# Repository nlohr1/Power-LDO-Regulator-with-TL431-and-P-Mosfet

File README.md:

# Power-LDO-Regulator with TL431 and P-Mosfet
Power-LDO to regulate voltages above +5V protecting USB-connectors from incoming overvoltages.

This Layout adds a simple way to eliminate dangerous incoming Over-Voltages on USB (above 5,25V) coming f.ex. from
odd Power-Supplies which don't acomplish the USB-specifications (but often are usable and cheap enough to be used as 5V-Supply).

Usually generic LDO-chips can output between 100 mAmp upto 1 Ampére. But what if you have a Power-Supply which can supply 4 or
more Amps but the voltage is too high for savely connect to the USB-Power-Input? (f.ex. on the new Raspberry Pi 4).
Most of commercial (Power-)LDO's need more than 3 Volts to be able to regulate the Output reliably. So the old LM7805 or even
the commonly used LM317(adj). And other mainly used chips as the AMS1117 normally only can provide upto 800mA. In most cases
this is sufficient power. But if you have a Power-Supply with an Output of (f.ex.) 5,5V and need to have an USB-Input with
a greater Power than 3 Amps, then you can go with this small layout, the board needing only few space (20 x 9 mm) and can
provide more than 4A – with a Heat-Sink and a more powerful Power-Mosfet even more than 10A...

Provided files here with 2 alternative solutions:
- first solution with a TL431-Shunt-Regulator + OPAmp and a *Power-P-Mosfet*,
- second solution with same TL431 + OPAmp but with a *Power-N-Mosfet*, due to this Mosfets generally have fewer resistance
  (=more "power"), are cheaper and there are more available types (of N-Mosfets) on the market (availability).

A caveat from this second solution is that it has only a common +5V line between Input and Output but no common Ground with the Main-Supply.
But on the other side this is mostly no problem for the End-Load, because the providing 5V-Main-Supplies normally are isolated-topologies,
so "GND" of the Destination-Load may be seen here simply as 5V-difference from our common +5V line.

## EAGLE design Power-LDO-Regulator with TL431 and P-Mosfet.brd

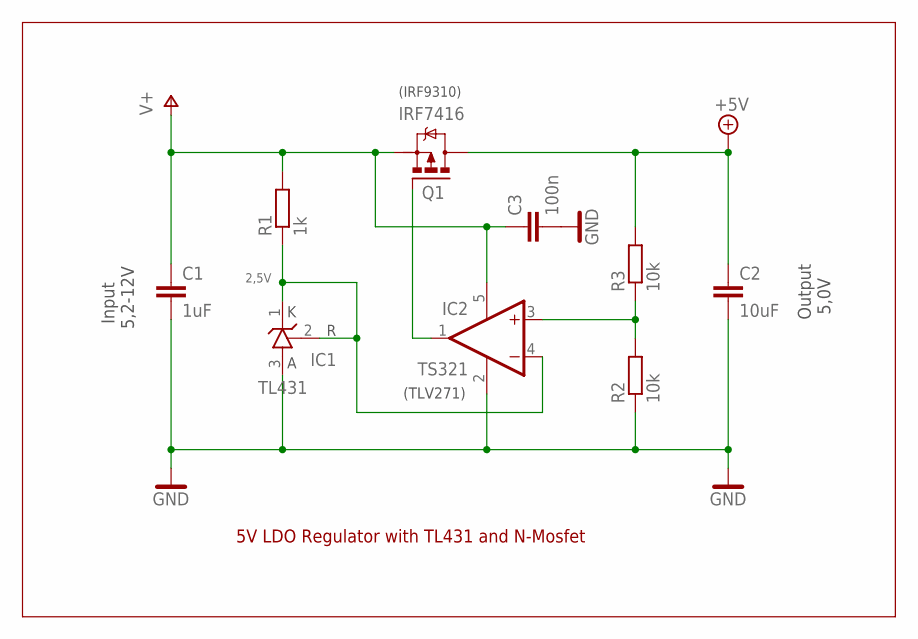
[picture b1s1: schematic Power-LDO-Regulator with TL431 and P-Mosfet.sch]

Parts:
C1: 1uF; C0805
C2: 10uF; C0805
C3: 100n; C0603
IC1: TL431; SOT23
IC2: TS321; SOT23-5
Q1: IRF7416; SO-08
R1: 1k; R0603
R2, R3: 10k; R0603

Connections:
+5V: C2.1, Q1.5 (D), Q1.6 (D), Q1.7 (D), Q1.8 (D), R3.2
GND: C1.2, C2.2, C3.2, IC1.3 (A), IC2.2 (GND), R2.1
unnamed: IC2.3 (+IN), R2.2, R3.1
unnamed: IC1.1 (C), IC1.2 (R), IC2.4 (-IN), R1.1
unnamed: IC2.1 (OUT), Q1.4 (G)
V+: C1.1, C3.1, IC2.5 (V+), Q1.1 (S), Q1.2 (S), Q1.3 (S), R1.2

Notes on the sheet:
5V LDO Regulator with TL431 and N-Mosfet
Input 5,2-12V
Output 5,0V
2,5V
(TLV271)
(IRF9310)

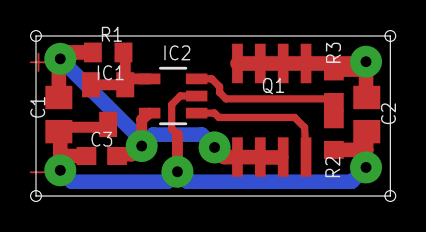
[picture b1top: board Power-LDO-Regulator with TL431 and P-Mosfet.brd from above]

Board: 2 copper layers, 19.7 x 8.9 mm, 9 parts (0 on the bottom side), 6 nets.
